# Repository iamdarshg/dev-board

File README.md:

# dev-real production board

Self-contained KiCad 9 project: board, schematics, project rules, and referenced
libraries. Open `dev-real-production.kicad_pro` for the production board; keep the
project file beside the board so DRC uses the intended rules.

## Current measured status (2026-11-04)

The repaired production board is at **10 DRC warnings, 0 errors, and 0
unconnected items**. This is not yet fab-ready. The warning breakdown is:

- 1 intentional JTDI dangling-track warning (deletion breaks a real connection)
- 2 intentional `/Power/SW` stacked microvia/blind-buried warnings requiring JLC HDI confirmation
- 2 intentional silk-only library mismatch warnings (RANT1/CANT1; shared-library deviations)
- 5 copper-sliver warnings requiring KiCad PCB Editor marker inspection

The ten hole-to-hole violations were fixed with KiCad-native geometry edits and
fresh DRC verification. The repaired board and library changes remain working-tree
state. Detailed evidence is in:
`../../evidence/dev-board/GEOMETRY_REPAIR_2026-11-02.md`.

A regenerated but not release-approved fabrication package is in:
`../../evidence/dev-board/fab-2026-11-02/`. Do not promote it to `E:\final order`
until the slivers and JLC stackup questions are closed.

---

## 1. Routing complete (historical)

All 14 unconnected items from the previous pass (was 499 originally) have
been resolved, including the last 6 hold-outs around the U13 radar BGA
corner (GND ball M12, an In2/GND stub near (56.9, 16.0), C34 pad 1, U21 pad
26, a split GND plane island on In1, and an NRESET In1↔F gap) — these needed
hand-routing (via-in-pad style connections plus small shoves of a couple of
neighboring nets — FT_RXD, GPIO_4 — that were routed directly under the
affected pads) since the escape-track congestion in that corner defeats the
interactive shove router's default settings. `Inspect → Design Rules
Checker → Run DRC` now reports **0 errors, 0 unconnected** with zones
refilled.

If future edits reintroduce unconnected items, the same workflow applies:

1. Open `dev-real.kicad_pro` → PCB Editor.
2. `Route → Interactive Router Settings…` → set **Mode: Shove** (Walk Around
   struggles near the U13 BGA corner, where several nets route directly
   under neighboring balls).
3. `Inspect → Design Rules Checker → Run DRC`, open the **Unconnected
   Items** tab, double-click an item to zoom to it.
4. Hover the pad → press `X` → route → double-click to finish. Press `V`
   mid-route to drop a via and switch layers.
5. Press `B` to refill all zones before the final DRC check — stale zone
   fill after a track/via edit can itself show up as a false clearance
   violation until refilled.

## 2. Fix SCOPE_BIAS in the schematic

`/AD9609/SCOPE_BIAS` has **no DC reference** anywhere in the schematic — the net
floats on the real board. Open `ad9609bcpzrl7_80_breakout.kicad_sch` and define
the intended bias source, then `Tools → Update PCB from Schematic` (F8).

## 3. Sanity-check before you save

After any edit: press `B` to refill zones, then `Inspect → Design Rules
Checker → Run DRC` and confirm it still reads **0 errors, 0 unconnected**
before `Ctrl+S`.

---

### Design rules already in effect (don't change)

Signal 0.127 mm / vias 0.254 mm with 0.127 mm drill / clearance 0.08 mm /
min through-drill 0.127 mm. Power rails run 0.2–0.5 mm.
The 0.2/0.1 vias on this board are **microvias** — place a new *through*-via
that small and DRC will (correctly) reject it.

### What's in here

- `dev-real.kicad_pcb` — the board
- `dev-real.kicad_pro` — project + design rules (**keep beside the board**;
  without it KiCad invents default rules and DRC becomes meaningless)
- `dev-real.kicad_sch` + 8 hierarchical sheets — full schematic
- `fp-lib-table`, `sym-lib-table` + the custom symbol/footprint libraries they
  reference (AD9609, IWRL6432, MM8108, THS8136, XCC1352, ICM-42670, ENS161,
  MMC5633, plus the project's `.pretty` footprint dirs)

Verified standalone: netlist exports all 318 components across the 9-sheet
hierarchy, and DRC output is identical to the working copy.

Full history, method, DRC report, renders and the routing scripts stay in
`D:\dev-real-updated\dev-real-updated\dev-real-routing-finish\`.

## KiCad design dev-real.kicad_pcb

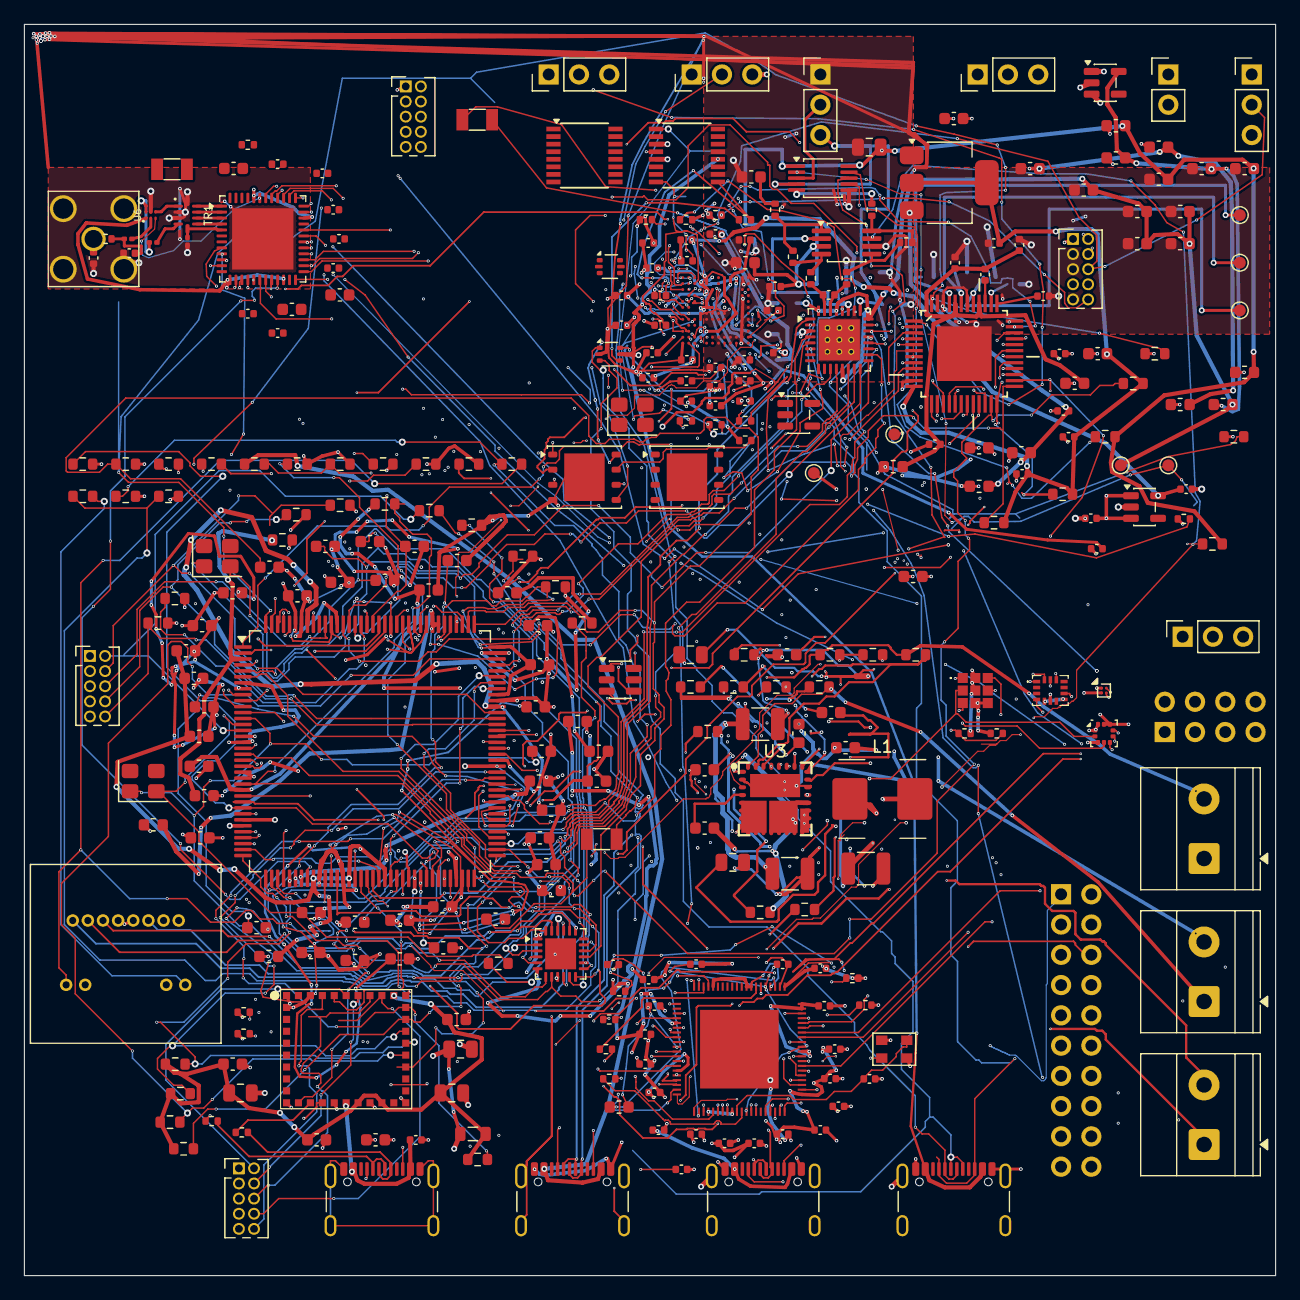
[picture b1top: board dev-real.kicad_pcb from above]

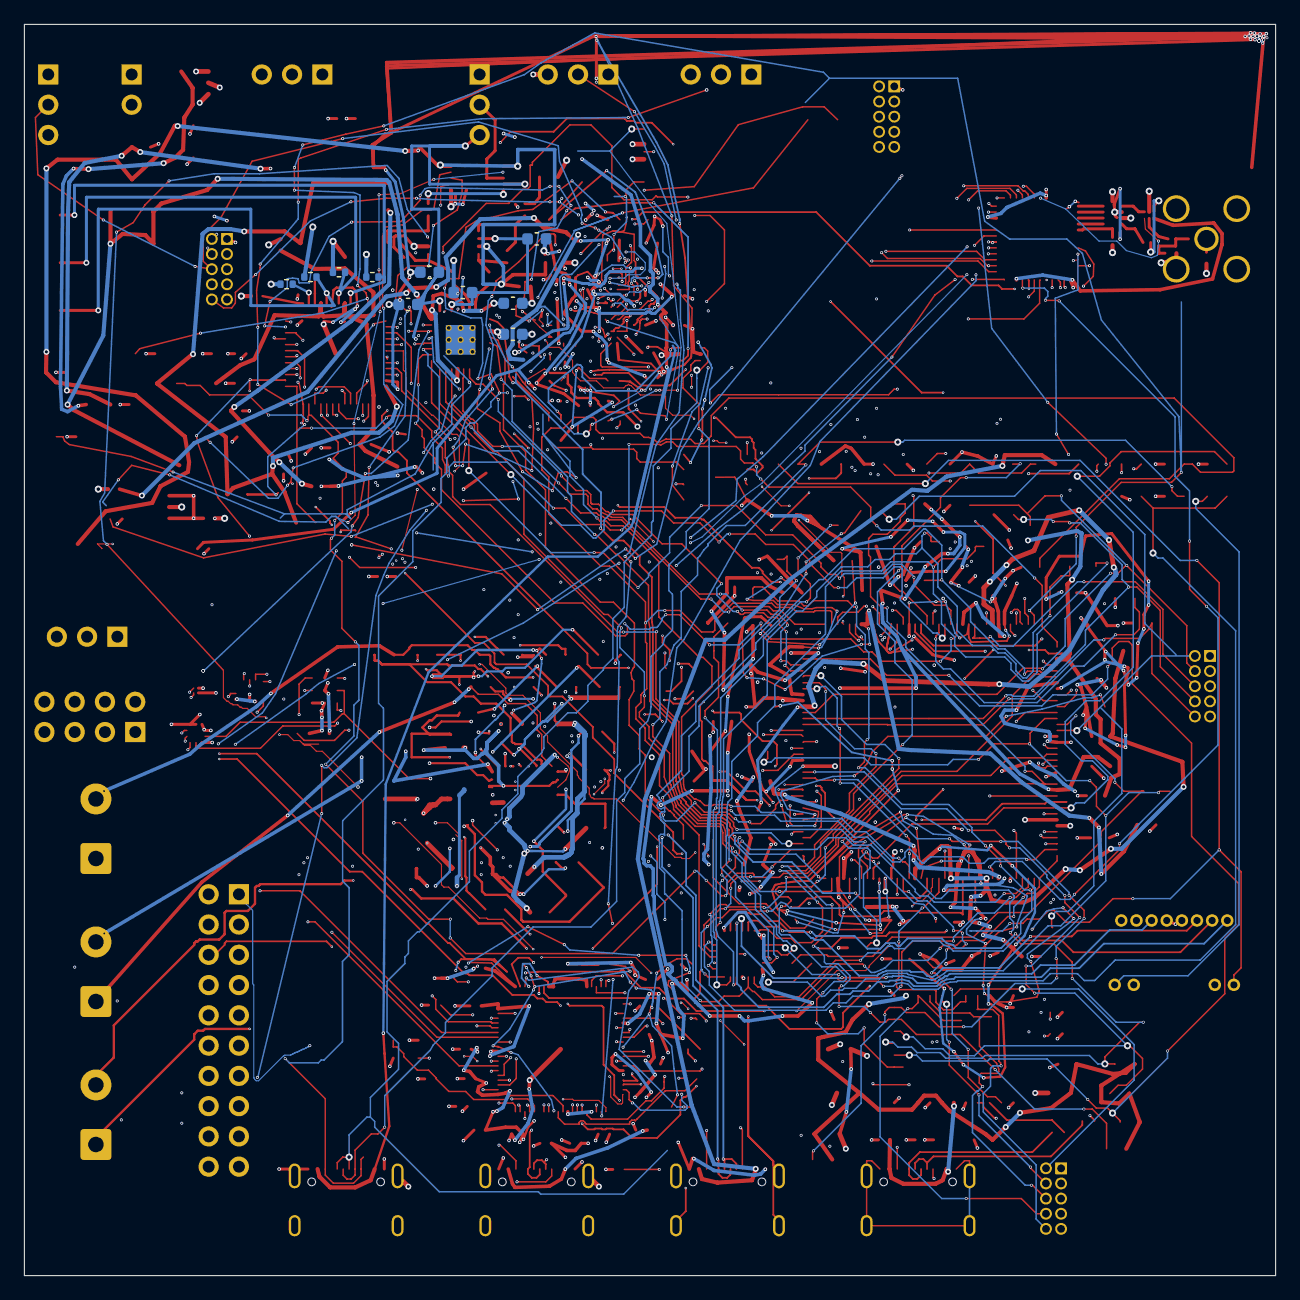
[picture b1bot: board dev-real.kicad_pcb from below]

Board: 4 copper layers, 105.0 x 105.0 mm, 318 parts (10 on the bottom side), 304 nets.

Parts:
C1: 4.7uF / >=10V; C_0805_2012Metric
C2: 2.2uF / >=10V; C_0603_1608Metric
C3, C5, C65, C69, C70, C75, C98, C99, C102, C106, C107, C109, C110, C112, C113, C114, C115, C116, C119, C120, C121, C122, C123, C124, C125, C126, C129, C130, C134: 100nF; C_0603_1608Metric
C4, C135: 4.7nF; C_0603_1608Metric
C6, C7: 15pF C0G; C_0402_1005Metric
C8, C9, C10: 4.7uF 6.3V X5R; C_0402_1005Metric
C11, C12, C14, C16, C17, C20, C34, C35, C45: 0.1uF; C_0402_1005Metric
C13, C15, C18: 22uF; C_0603_1608Metric
C19, C26, C27, C37, C40, C49, C54, C61: 1uF; C_0402_1005Metric
C21, C22, C23: 100pF; C_0201_0603Metric
C24, C25: 4.7pF; C_0402_1005Metric
C28, C39: 0.22uF; C_0402_1005Metric
C29, C30: 22pF; C_0402_1005Metric
C31, C33, C41, C42, C43: 2.2uF; C_0402_1005Metric
C32: 0.047uF; C_0402_1005Metric
C36, C38, C44, C46, C47: 10uF; C_0402_1005Metric
C48: 4.7uF; C_0402_1005Metric
C50, C52, C53, C60, C71, C76, C77, C83: 10uF; C_0603_1608Metric
C51, C55, C56, C57, C58, C59, C62, C63: 100nF; C_0402_1005Metric
C64, C67, C74: 10uF; C_0805_2012Metric
C66: 22uF; C_0805_2012Metric
C68, C78, C84, C89, C103, C118, C131, C132: 1uF; C_0603_1608Metric
C72, C79, C81, C85, C86, C87, C88, C92, C93: 100n; C_0603_1608Metric
C73: 100nF BIAS; C_0603_1608Metric
C80: 100nF AVDD; C_0603_1608Metric
C82: 100nF DVDD; C_0603_1608Metric
C90: 100nF VDD; C_0603_1608Metric
C91: 100nF VOCM; C_0603_1608Metric
C94: 1nF VDD HF; C_0402_1005Metric
C95: 22pF C0G; C_0402_1005Metric
C96, C101: 12pF; C_0603_1608Metric
C97, C105, C111: 2.2uF low-ESR; C_0603_1608Metric
C100, C104: 4.7uF; C_0603_1608Metric
C108, C117: 6.8pF; C_0603_1608Metric
C127, C128: 18pF; C_0603_1608Metric
C133: 2.2uF; C_0603_1608Metric
CANT1, CANT2: DNP; C_0402_1005Metric
CIN1: 10uF / >=10V; C_1210_3225Metric
CIN2: 39uF / >=10V; C_1210_3225Metric
COUT1: 47uF / >=6.3V; C_1210_3225Metric
COUT2: 100uF / >=6.3V; C_TODO_SELECT_100uF
CSS1: 12nF; C_0603_1608Metric
CSVIN1: 1uF / >=10V; C_0805_2012Metric
C_ADC1: 100nF; C_0402_1005Metric
C_DVDD1, C_DVDD2, C_DVDD3: 100nF; C_0402_1005Metric
C_IOBULK1: 10uF; C_0402_1005Metric
C_IOVDD1, C_IOVDD2, C_IOVDD3, C_IOVDD4, C_IOVDD5, C_IOVDD6, C_IOVDD7, C_IOVDD8: 100nF; C_0402_1005Metric
C_QSPI1: 100nF; C_0402_1005Metric
C_USB1, C_USB2: 100nF; C_0402_1005Metric
C_USBOTP1: 100nF; C_0402_1005Metric
FB1, FB2, FB4, FB5, FB6: 600R@100MHz; L_0603_1608Metric
FB3: 600R@100MHz; L_0805_2012Metric
FB7, FB8, FB9: 600R@100MHz; L_0603_1608Metric_Pad0.95x0.95mm_HandSolder
IC1: ICM-42670-P; ICM42670P
IC2: ENS161-BLGT_LGA9_T&R_1k5; ENS161BLGTLGA9TR1k5
J1: VIN_IN; TerminalBlock_Phoenix_MKDS-1,5-2_1x02_P5.00mm_Horizontal
J2: TP_EN_PG; TerminalBlock_Phoenix_MKDS-1,5-2_1x02_P5.00mm_Horizontal
J3: TP_SW_FB; TerminalBlock_Phoenix_MKDS-1,5-2_1x02_P5.00mm_Horizontal
J4, J17: USB-C Receptacle USB2; USB_C_Receptacle_GCT_USB4105-xx-A_16P_TopMnt_Horizontal
J5: Conn_01x03_Pin; PinSocket_1x03_P2.54mm_Vertical
J6: ARM_Cortex_Debug_10; PinHeader_2x05_P1.27mm_Vertical
J7: SMA_ANT_50OHM; SMA_Molex_73251-2120_EdgeMount_Horizontal
J8: 3V3_IN; PinHeader_1x02_P2.54mm_Vertical
J10: USB-C USB2 DEBUG; USB_C_Receptacle_GCT_USB4105-xx-A_16P_TopMnt_Horizontal
J11, J16: ARM_JTAG_10; PinHeader_2x05_P1.27mm_Vertical
J12: SOP0_SELECT; PinHeader_1x03_P2.54mm_Vertical
J13: SOP1_SELECT; PinHeader_1x03_P2.54mm_Vertical
J14, J15: Conn_01x03; PinHeader_1x03_P2.54mm_Vertical
J18: Conn_01x03_Pin; PinHeader_1x03_P2.54mm_Vertical
J19: Cortex SWD/JTAG; PinHeader_2x05_P1.27mm_Vertical
J20: USB-C USB2 DEVICE; USB_C_Receptacle_GCT_USB4105-xx-A_16P_TopMnt_Horizontal
J21: HR911105A MAGJACK; RJ45_Hanrun_HR911105A
J22: Conn_02x10_Counter_Clockwise; PinHeader_2x10_P2.54mm_Vertical
J23: Conn_02x04_Odd_Even; PinHeader_2x04_P2.54mm_Vertical
L1: 1uH LMLP07C7M1R0DTAS, Idc 15A / Isat 20A; L_Kyocera_LMLP07C7D_7.3x6.6mm
L2: 3.3uH Abracon AOTA-B201610S3R3-101-T; L_Abracon_AOTA-B201610S_2.0x1.6mm
NT1: AGND_to_PGND_single_point; NetTie-2_SMD_Pad0.5mm
R1, R35, R43, R46, R47, R48, R49, R62: 100k; R_0603_1608Metric
R2: 60.4k; R_0603_1608Metric
R3, R4: 2R; R_0603_1608Metric
R5: 24.3k; R_0603_1608Metric
R6, R70, R71: 1k; R_0402_1005Metric
R7, R8, R28, R29: 27R; R_0402_1005Metric
R9: 33R 1%; R_0402_1005Metric
R10: 100k; R_0402_1005Metric
R11, R12: 10k; R_0402_1005Metric
R13, R14: 27; R_0402_1005Metric
R15, R16: 0; R_0402_1005Metric
R17: 47.5k; R_0402_1005Metric
R18, R19: 2M; R_0402_1005Metric
R20, R21, R22: 75R; R_0402_1005Metric
R23, R24, R25, R27: 2.2k; R_0603_1608Metric
R26: 3.8k; R_0402_1005Metric
R30, R31, R32, R33, R34: 47k; R_0603_1608Metric
R36, R37, R39, R40: 1k 0.1%; R_0402_1005Metric
R38: 10k 1%; R_0603_1608Metric
R41, R42: 33R; R_0402_1005Metric
R44, R50: 0R; R_0603_1608Metric
R45, R65: 1M; R_0603_1608Metric
R51, R52, R53, R54, R55, R57: 10k; R_0603_1608Metric
R56: 1.5k; R_0603_1608Metric
R58, R59: 22R; R_0603_1608Metric
R60: 100R; R_0603_1608Metric
R61: 12.1k 1%; R_0603_1608Metric
R63, R64: 5.1k; R_0603_1608Metric
R66, R67: 330R; R_0603_1608Metric
R68, R69: 10k STRAP LOW; R_0603_1608Metric
RANT1: 0R; R_0402_1005Metric
RBOT1: 665R; R_0603_1608Metric
RCC1, RCC2, RCC3, RCC4: 5.1k; R_0402_1005Metric
RCL1: 2.21k; R_0603_1608Metric
REN1: 100k; R_0603_1608Metric
REXTVDD1: 0R DNP/NC option; R_0603_1608Metric
RPG1: 10k; R_0603_1608Metric
RTOP1: 3.00k; R_0603_1608Metric
TP1: AR_TP; TestPoint_Pad_D1.0mm
TP2: AG_TP; TestPoint_Pad_D1.0mm
TP3: AB_TP; TestPoint_Pad_D1.0mm
TP4, TP5: VCM; TestPoint_Pad_D1.0mm
TP6: VREF; TestPoint_Pad_D1.0mm
TP7: AVDD_1V8; TestPoint_Pad_D1.0mm
TR1: 0900PC15A0036; Johanson_0900PC15A0036_0805_10Pin
U1: MMC5633NJL; WLP-4_0.86x0.86mm_P0.4mm
U2: LPS22HH; ST_HLGA-10_2x2mm_P0.5mm_LayoutBorder3x2y
U3: MIC28516T-E/PHA; MIC28516-VQFN-32-6x6mm-P0.65-MultipleEP
U4: RP2350B; RP2350B_QFN80_10x10mm_P0.4mm_EP
U5: XCC1352R1F3RGZR; VQFN-48-1EP_7x7mm_P0.5mm_EP5.15x5.15mm
U6: XMSSJJ3G0PA-054; Murata_XMSSJJ3G0PA-054
U7: TLV75518PDBV; SOT-23-5
U8: TLV75518PDBVR; SOT-23-5
U9, U10: USBLC6-2P6; SOT-666
U11, U12: FT230XS-R; SSOP-16_3.9x4.9mm_P0.635mm
U13: IWRL6432BDBAAMFR; IWRL6432_AMF_FCCSP-102_6.45x6.45mm_P0.50mm
U14, U15: MX25R1635FZUIH0; WSON-8-1EP_6x5mm_P1.27mm_EP3.4x4mm
U16: AMS1117-1.8; SOT-223-3_TabPin2
U17: THS8136; QFP50P900X900X120-49N
U18: MM8108-MF15457; MM8108MF15457
U19: AP2112K-1.8; SOT-23-5
U20: PGA113AIDGSR; VSSOP-10_3x3mm_P0.5mm
U21: AD9609BCPZRL7-80; QFN-32-1EP_5x5mm_P0.5mm_EP3.45x3.45mm_ThermalVias
U22: MCP6D11T-E/MS; MSOP-8_3x3mm_P0.65mm
U23: STM32H7S3Z8T6; LQFP-144_20x20mm_P0.5mm
U24: LAN8742A-CZ-TR; QFN-24-1EP_4x4mm_P0.5mm_EP2.6x2.6mm
U25: USBLC6-2SC6; SOT-23-6
Y1: 12MHz ABM8-272-T3; Crystal_ABM8_3.2x2.5mm
Y2: 48MHz; Crystal_SMD_3225-2Pin_3.2x2.5mm
Y3: 40MHz; Crystal_SMD_3225-2Pin_3.2x2.5mm
Y4: 40MHz; Crystal_SMD_3225-4Pin_3.2x2.5mm
Y5: 24MHz; Crystal_SMD_3225-4Pin_3.2x2.5mm
Y6: 32.768kHz; Crystal_SMD_3215-2Pin_3.2x1.5mm
Y7: 25MHz; Crystal_SMD_3225-4Pin_3.2x2.5mm

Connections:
+3V3: C4.1, C8.1, C26.2, C31.2, C36.2, C45.2, C49.2, C50.2, C51.2, C64.1, C65.1, C71.2, C72.2, C98.1, C99.1, C100.1, C106.1, C107.1, C112.1, C113.1, C115.1, C116.1, C120.1, C121.1, C124.1, C125.1, C130.1, C131.1, COUT1.1, COUT2.1, C_ADC1.1, C_IOBULK1.1, C_IOVDD1.1, C_IOVDD2.1, C_IOVDD3.1, C_IOVDD4.1, C_IOVDD5.1, C_IOVDD6.1, C_IOVDD7.1, C_IOVDD8.1, C_QSPI1.1, C_USBOTP1.1, FB1.1, FB2.1, FB3.1, FB4.1, FB5.1, FB7.1, FB8.1, FB9.1, IC1.5 (VDDIO), IC1.8 (VDD), IC2.4 (VDD), IC2.5 (VDDIO), J6.1, J11.1, J14.3, J15.3, J19.9, J21.4, J21.5, J22.2, J22.3, J23.6, L1.2, R9.1, R12.1, R17.1, R18.1, R19.1, R44.2, R46.2, R49.2, R51.2, R53.2, R54.2, R55.2, R56.2, R57.2, R71.1, RTOP1.1, U1.B1 (VDD), U2.1 (Vdd_IO), U2.10 (VDD), U4.5, U4.15, U4.24, U4.29, U4.41, U4.50, U4.59, U4.60, U4.64, U4.68, U4.69, U4.76, U5.13 (VDDS2), U5.22 (VDDS3), U5.34 (VDDS_DCDC), U5.44 (VDDS), U6.1, U7.1 (IN), U7.3 (EN), U12.3 (VCCIO), U13.G12 (VIOIN), U13.M11 (VIOIN), U14.8 (VCC), U19.1 (VIN), U19.3 (EN), U23.7 (VDD), U23.17 (VDD), U23.31 (VDD), U23.41 (VDD), U23.69 (VDD), U23.81 (VDD), U23.88 (VDD), U23.100 (VDD), U23.108 (VDD), U23.123 (VDD), U23.133 (VDD), U23.139 (VDD), U24.1 (VDD2A), U24.9 (VDDIO), U24.19 (VDD1A)
/AD9609/3V3_AFE: C74.2, C75.2, C80.2, C82.2, C90.2, C94.2, FB4.2, R35.2, R43.2, U20.1 (AVDD), U20.10 (DVDD), U22.3 (VDD)
/AD9609/ADC_VIN_N: C95.1, R42.1, U21.30 (VIN-)
/AD9609/ADC_VIN_P: C95.2, R41.1, U21.31 (VIN+)
/AD9609/AVDD_1V8: C83.2, C84.2, C85.2, C86.2, C87.2, C88.2, FB6.2, TP7.1, U21.13 (DRVDD), U21.24 (AVDD), U21.29 (AVDD), U21.32 (AVDD)
/AD9609/CLK_N: U21.2 (CLK-), U23.61 (PP1)
/AD9609/CLK_P: U21.1 (CLK+), U23.55 (PP0)
/AD9609/CSB: U21.4 (CSB), U23.83 (PD15)
/AD9609/D0: U21.11 (D0), U23.104 (PD0)
/AD9609/D1: U21.12 (D1), U23.105 (PD1)
/AD9609/D2: U21.14 (D2), U23.71 (PD12)
/AD9609/D3: U21.15 (D3), U23.109 (PD3)
/AD9609/D4: U21.16 (D4), U23.129 (PD5)
/AD9609/D5: U21.17 (D5), U23.130 (PD6)
/AD9609/D6: U21.18 (D6), U23.131 (PD7)
/AD9609/D7: U21.19 (D7), U23.65 (PD8)
/AD9609/D8: U21.20 (D8), U23.66 (PD9)
/AD9609/D9: U21.21 (D9), U23.67 (PD10)
/AD9609/DCO: U21.22 (DCO), U23.68 (PD11)
/AD9609/DRVDD_3V3: C76.2, C78.2, C81.2, FB5.2, U21.3 (AVDD)
/AD9609/LDO_1V8: C77.2, C79.2, FB6.1, U19.5 (VOUT)
/AD9609/MCP_IN_N: R36.1, R39.2, U22.1 (IN-)
/AD9609/MCP_IN_P: R37.1, R40.2, U22.8 (IN+)
/AD9609/MCP_OUT_N: R40.1, R42.2, U22.5 (OUT-)
/AD9609/MCP_OUT_P: R39.1, R41.2, U22.4 (OUT+)
/AD9609/MODE_OR: U21.23 (MODE/OR), U23.82 (PD14)
/AD9609/PGA_OUT: R37.2, U20.5 (VOUT)
/AD9609/RBIAS: R38.2, U21.28 (RBIAS)
/AD9609/SCLK_DFS: U21.5 (SCLK/DFS), U23.72 (PD13)
/AD9609/SCOPE_BIAS: C73.2, R36.2
/AD9609/SCOPE_DRIVER_PD_N: R43.1, U22.7 (~PD), U23.54 (PP5)
/AD9609/SCOPE_PGA_CS_N: R35.1, U20.9 (~CS), U23.47 (PP4)
/AD9609/SCOPE_PGA_DIO: U20.8 (DIO), U23.49 (PP3)
/AD9609/SCOPE_PGA_SCLK: U20.7 (SCLK), U23.48 (PP2)
/AD9609/SDIO_PDWN: U21.6 (SDIO/PDWN), U23.58 (PP6)
/AD9609/VCM: C91.2, C93.2, TP5.1, U21.27 (VCM), U22.2 (VOCM)
/AD9609/VREF: C89.2, C92.2, J18.3, TP6.1, U20.4 (VREF), U21.25 (VREF)
/IWRL6432BD/1V8: C27.2, C39.2, C42.2, C46.2, U7.5 (OUT), U13.C6 (VIOIN_18CLK), U13.C8 (VIOIN_18), U13.F3 (VDDA_18VCO), U13.J5 (VIN_18PM), U13.K12 (VIOIN_18), U13.L5 (VDDA_18BB), U13.L8 (VIOIN_18), U13.M5 (VDDA_18BB), U13.M8 (VIOIN_18)
/IWRL6432BD/FT_RXD: R16.1, U12.4 (RXD)
/IWRL6432BD/FT_TXD: R15.1, U12.1 (TXD)
/IWRL6432BD/FT_USBDM: C29.2, R13.2, U12.9 (USBDM)
/IWRL6432BD/FT_USBDP: C30.2, R14.2, U12.8 (USBDP)
/IWRL6432BD/GPIO_0: U4.16, U13.B12 (SPIA_MOSI/GPIO_0)
/IWRL6432BD/GPIO_1: U4.17, U13.C11 (SPIA_MISO/GPIO_1)
/IWRL6432BD/GPIO_2: U4.18, U13.H10 (GPIO_2)
/IWRL6432BD/GPIO_3: U4.19, U13.J11 (UARTA_RX/GPIO_3)
/IWRL6432BD/GPIO_4: U4.20, U13.K11 (NERROR_OUT/GPIO_4)
/IWRL6432BD/GPIO_5: U4.21, U13.J10 (GPIO_5)
/IWRL6432BD/GPIO_6: U4.22, U13.L11 (UARTA_RTS/GPIO_6)
/IWRL6432BD/GPIO_7: U4.23, U13.M10 (HOST_CLK_REQ/GPIO_7)
/IWRL6432BD/JTAG_TCK: J11.4, U13.C12 (TCK)
/IWRL6432BD/JTAG_TDI: J11.8, U13.G11 (TDI)
/IWRL6432BD/JTAG_TMS: J11.2, U13.E12 (TMS)
/IWRL6432BD/NRESET: C28.2, J11.10, R12.2, U13.L10 (NRESET)
/IWRL6432BD/PMIC_CLKOUT_SOP1: J15.2, U13.H11 (PMIC_CLKOUT/SOP1)
/IWRL6432BD/QSPI_CLK: U13.A11 (QSPI_CLK), U14.6 (SCLK)
/IWRL6432BD/QSPI_CS: R17.2, U13.A10 (QSPI_CS), U14.1 (CS#)
/IWRL6432BD/QSPI_D0: U13.B11 (QSPI[0]), U14.5 (SI/SIO0)
/IWRL6432BD/QSPI_D1: U13.B8 (QSPI[1]), U14.2 (SO/SIO1)
/IWRL6432BD/QSPI_D2: R18.2, U13.B10 (QSPI[2]), U14.3 (WP#/SIO2)
/IWRL6432BD/QSPI_D3: R19.2, U13.B9 (QSPI[3]), U14.7 (RESET#/SIO3)
/IWRL6432BD/RADAR_1P2_RF: C41.2, C44.2, U13.L4 (VDDA_12RF), U13.M4 (VDDA_12RF)
/IWRL6432BD/RADAR_1V2_INT: C48.2, U13.C9 (VDD), U13.G7 (VDD), U13.G8 (VDD), U13.G9 (VDD), U13.H8 (VDD), U13.K7 (VDD)
/IWRL6432BD/RADAR_1V4_APLL: C37.2, U13.G5 (VOUT_14APLL)
/IWRL6432BD/RADAR_1V4_SYNTH: C40.2, U13.D3 (VOUT_14SYNTH)
/IWRL6432BD/RADAR_1V_RF_OUT: C33.2, C38.2, U13.L3 (VDDA_10RF), U13.M3 (VDDA_10RF)
/IWRL6432BD/RADAR_SRAM_1V2: C43.2, C47.2, U13.L9 (VNWA), U13.M7 (VDD_SRAM)
/IWRL6432BD/RADAR_VBGAP: C32.2, U13.H5 (VBGAP)
/IWRL6432BD/RDIF_D2: U4.25, U13.L12 (UARTA_TX)
/IWRL6432BD/RS232_RX: R15.2, U13.F11 (RS232_RX)
/IWRL6432BD/RS232_TX: R16.2, U13.E10 (RS232_TX)
/IWRL6432BD/TDO_SOP0: J11.6, J14.2, U13.E11 (TDO/SOP0)
/IWRL6432BD/USB_DM_CONN: J10.A7 (D-), J10.B7 (D-), U9.3 (I/O2)
/IWRL6432BD/USB_DP_CONN: J10.A6 (D+), J10.B6 (D+), U9.1 (I/O1)
/IWRL6432BD/USB_ID: J10.A5 (CC1), J10.B5 (CC2), R11.1
/IWRL6432BD/USB_VBUS: C34.2, J10.A4 (VBUS), J10.A9 (VBUS), J10.B4 (VBUS), J10.B9 (VBUS), U9.5 (VBUS), U12.12 (VCC)
/IWRL6432BD/XTALM: C24.2, U13.B1 (CLKM), Y3.1
/IWRL6432BD/XTALP: C25.2, U13.D1 (CLKP), Y3.2
/MM8108/3V3_MM8108: C66.1, C67.1, C68.1, C69.1, C70.1, FB3.2, R30.1, R31.1, R32.1, R33.1, R34.1, U18.10 (VBAT), U18.22 (VDDIO), U18.24 (VBAT_TX)
/MM8108/BUSY: U18.29 (BUSY), U23.59 (PO2)
/MM8108/JTAG_TCK: J16.4, U18.7 (JTAG_TCK/GPIO13)
/MM8108/JTAG_TDI: J16.8, U18.9 (JTAG_TDI/GPIO14)
/MM8108/JTAG_TMS: J16.2, U18.6 (JTAG_TMS/GPIO15)
/MM8108/NRESET: J16.10, U18.4 (RESET_N)
/MM8108/SDIO_CLK_SPI_SCK: U18.17 (SDIO_CLK/SPI_SCK), U23.103 (PC12)
/MM8108/SDIO_CMD_SPI_MOSI: R34.2, U18.16 (SDIO_CMD/SPI_MOSI), U23.106 (PD2)
/MM8108/SDIO_D0_SPI_MISO: R30.2, U18.12 (SDIO_D0/SPI_MISO), U23.86 (PC8)
/MM8108/SDIO_D1_SPI_INT: R31.2, U18.14 (SDIO_D1/SPI_INT), U23.87 (PC9)
/MM8108/SDIO_D2: R32.2, U18.15 (SDIO_D2), U23.101 (PC10)
/MM8108/SDIO_D3_SPI_CS: R33.2, U18.13 (SDIO_D3/SPI_CS), U23.102 (PC11)
/MM8108/TDO_SOP0: J16.6, U18.8 (JTAG_TDO/GPIO16)
/MM8108/WAKE: U18.5 (WAKE), U23.53 (PO4)
/Power/AGND: CSS1.2, CSVIN1.2, NT1.1, R2.2, RBOT1.2, U3.28
/Power/BST: C3.1, U3.4
/Power/EN: J2.2, REN1.2, U3.24
/Power/EXTVDD: REXTVDD1.1, U3.23
/Power/FB: C4.2, C5.2, J3.1, RBOT1.1, RTOP1.2, U3.27
/Power/FREQ: R1.2, R2.1, U3.25
/Power/ILIM: RCL1.1, U3.1
/Power/MODE_SS: CSS1.1, U3.26
/Power/PG: J2.1, RPG1.2, U3.32
/Power/PVDD: C1.1, R4.2, U3.21
/Power/RIPPLE_INJ: C5.1, R5.2
/Power/SVIN: CSVIN1.1, R3.2, U3.31
/Power/SW: C3.2, J3.2, L1.1, R5.1, RCL1.2, U3.3, U3.12, U3.13, U3.14, U3.15, U3.20
/Power/VDD: C2.1, R4.1, REN1.1, RPG1.1, U3.30
/Power/VIN: CIN1.1, CIN2.1, J1.2, R1.1, R3.1, U3.5, U3.6, U3.7, U3.8, U3.9, U3.10, U3.11
/RP2350/+1V1: C9.1, C_DVDD1.1, C_DVDD2.1, C_DVDD3.1, L2.2, U4.10, U4.32, U4.51, U4.65
/RP2350/CC1: J4.A5 (CC1), RCC1.1
/RP2350/CC2: J4.B5 (CC2), RCC2.1
/RP2350/GPIO0: U4.77, U23.93 (PA11)
/RP2350/GPIO1: U4.78, U23.94 (PA12)
/RP2350/GPIO2: U4.79, U5.10 (DIO_5)
/RP2350/GPIO3: U4.80, U5.14 (DIO_8)
/RP2350/GPIO4: U4.1, U5.11 (DIO_6)
/RP2350/GPIO6: U4.3, U5.15 (DIO_9)
/RP2350/GPIO7: U4.4, U5.9 (DIO_4)
/RP2350/GPIO8: U4.6, U5.8 (DIO_3)
/RP2350/GPIO9: U4.7, U23.29 (PA3)
/RP2350/GPIO10: U4.8, U23.32 (PA4)
/RP2350/GPIO11: U4.9, U23.33 (PA5)
/RP2350/GPIO12: U4.11, U23.34 (PA6)
/RP2350/GPIO13: U4.12, U23.90 (PA8)
/RP2350/GPIO14: U4.13, U23.91 (PA9)
/RP2350/GPIO15: U4.14, U23.92 (PA10)
/RP2350/GPIO25: U2.7 (INT_DRDY), U4.26
/RP2350/GPIO26: IC1.4 (INT1_/_INT), U4.27
/RP2350/GPIO27: IC1.9 (INT2), U4.28
/RP2350/GPIO28: IC2.6 (INTN), U4.36
/RP2350/GPIO29: J23.4, U4.37
/RP2350/GPIO30: U1.B2 (SDA), U4.38
/RP2350/GPIO31: U1.A2 (SCL), U4.39
/RP2350/GPIO32: IC1.1 (AP_SDO_/_AP_AD0), U4.40
/RP2350/GPIO33: IC1.12 (AP_CS), U4.42
/RP2350/GPIO34: IC1.13 (AP_SCL_/_AP_SCLK), U4.43
/RP2350/GPIO35: IC1.14 (AP_SDA_/_AP_SDIO_/_AP_SDI), U4.44
/RP2350/GPIO36: IC2.1 (MOSI_/_SDA), U2.4 (SDA), U4.45
/RP2350/GPIO37: IC2.2 (SCLK_/_SCL), U2.2 (SCL), U4.46
/RP2350/GPIO38: IC2.7 (CSN), U4.47
/RP2350/GPIO39: U2.6 (~CS), U4.48
/RP2350/GPIO40_ADC0: U2.5 (SA0), U4.49
/RP2350/GPIO41_ADC1: IC2.3 (MISO_/_ADDR), U4.52
/RP2350/GPIO42_ADC2: R70.1, R71.2, U4.53
/RP2350/GPIO43_ADC3: J23.7, U4.54
/RP2350/GPIO44_ADC4: J23.5, U4.55
/RP2350/GPIO45_ADC5: J23.3, U4.56
/RP2350/GPIO46_ADC6: J23.1, U4.57
/RP2350/GPIO47_ADC7: J23.2, U4.58
/RP2350/SWCLK: J5.3, U4.33
/RP2350/SWDIO: J5.1, U4.34
/RP2350/USB_DM_IC: R8.1, U4.66
/RP2350/USB_DP_IC: R7.1, U4.67
/RP2350/USB_D_N_CONN: J4.A7 (D-), J4.B7 (D-), R8.2
/RP2350/USB_D_P_CONN: J4.A6 (D+), J4.B6 (D+), R7.2
/RP2350/USB_VBUS: C_USB1.1, J4.A4 (VBUS), J4.A9 (VBUS), J4.B4 (VBUS), J4.B9 (VBUS)
/RP2350/VREG_AVDD: C10.1, R9.2, U4.61
/RP2350/VREG_LX: L2.1, U4.63
/RP2350/XIN: C6.1, U4.30, Y1.2 (GND)
/RP2350/XOUT: R6.1, U4.31
/RP2350/XOUT_XTAL: C7.1, R6.2, Y1.4 (GND)
/STM32H7/3V3_USB: C132.1, C134.1, FB9.2, U23.115 (VDD50USB), U23.116 (VDD33USB)
/STM32H7/3V3_XSPI: C104.1, C110.1, C114.1, C119.1, C123.1, FB8.2, U23.45 (VDDXSPI1), U23.51 (VDDXSPI1), U23.57 (VDDXSPI1), U23.63 (VDDXSPI1)
/STM32H7/BOOT0: R47.1, U23.128 (BOOT0)
/STM32H7/ETH_CRS_DV: R55.1, U23.35 (PA7), U24.11 (CRS_DV/MODE2)
/STM32H7/ETH_LED1: R66.1, R68.1, U24.3 (LED1)
/STM32H7/ETH_LED2: R67.1, R69.1, U24.2 (LED2)
/STM32H7/ETH_MDC: U23.19 (PC1), U24.13 (MDC)
/STM32H7/ETH_MDIO: R56.1, U23.28 (PA2), U24.12 (MDIO)
/STM32H7/ETH_PHY_RESET: C126.1, R57.1, U23.110 (PD4), U24.15 (~RST)
/STM32H7/ETH_REF_CLK: U23.27 (PA1), U24.14 (~INT/REFCLKO)
/STM32H7/ETH_RXD0: R53.1, U23.36 (PC4), U24.8 (RXD0/MODE0)
/STM32H7/ETH_RXD1: R54.1, U23.37 (PC5), U24.7 (RXD1/MODE1)
/STM32H7/ETH_TXD0: U23.38 (PB0), U24.17 (TXD0)
/STM32H7/ETH_TXD1: U23.39 (PB1), U24.18 (TXD1)
/STM32H7/ETH_TX_EN: U23.74 (PB11), U24.16 (TXEN)
/STM32H7/HSE_IN: C96.1, R45.1, U23.13 (PH0), Y5.1
/STM32H7/HSE_OUT: C101.1, R45.2, U23.14 (PH1), Y5.2
/STM32H7/JTDI: J19.4, R49.1, U23.97 (PA15)
/STM32H7/LSE_IN: C108.1, U23.5 (PC14), Y6.1
/STM32H7/LSE_OUT: C117.1, U23.6 (PC15), Y6.2
/STM32H7/NRST: C122.1, J19.2, R51.1, U23.15 (NRST)
/STM32H7/PB2: U17.3 (B7), U23.40 (PB2)
/STM32H7/PB5: U17.4 (B6), U23.136 (PB5)
/STM32H7/PB6: U17.5 (B5), U23.143 (PB6)
/STM32H7/PB10: U17.26 (CLK), U23.73 (PB10)
/STM32H7/PB13: U17.20 (R7), U23.76 (PB13)
/STM32H7/PB14: U17.21 (R8), U23.77 (PB14)
/STM32H7/PB15: U17.22 (R9), U23.78 (PB15)
/STM32H7/PC0: U17.10 (B0), U23.18 (PC0)
/STM32H7/PC2: U17.9 (B1), U23.20 (PC2)
/STM32H7/PC3: U17.8 (B2), U23.21 (PC3)
/STM32H7/PC6: U17.7 (B3), U23.84 (PC6)
/STM32H7/PC7: U17.6 (B4), U23.85 (PC7)
/STM32H7/PC13: U17.27 (G9), U23.4 (PC13)
/STM32H7/PE0: U17.13 (R0), U23.140 (PE0)
/STM32H7/PE1: U17.14 (R1), U23.141 (PE1)
/STM32H7/PE2: U17.15 (R2), U23.142 (PE2)
/STM32H7/PE3: U17.16 (R3), U23.9 (PE3)
/STM32H7/PE4: U17.17 (R4), U23.10 (PE4)
/STM32H7/PE5: U17.18 (R5), U23.11 (PE5)
/STM32H7/PE6: U17.19 (R6), U23.12 (PE6)
/STM32H7/PHY_RBIAS: R61.1, U24.24 (RBIAS)
/STM32H7/PHY_RXER: R52.1, U24.10 (RXER/PHYAD0)
/STM32H7/PHY_RXN: J21.6, U24.22 (RXN)
/STM32H7/PHY_RXP: J21.3, U24.23 (RXP)
/STM32H7/PHY_TXN: J21.2, U24.20 (TXN)
/STM32H7/PHY_TXP: J21.1, U24.21 (TXP)
/STM32H7/PHY_VDDCR: C133.1, U24.6 (VDDCR)
/STM32H7/PHY_XTAL1: C127.1, U24.5 (XTAL1/CLKIN), Y7.1
/STM32H7/PHY_XTAL2: C128.1, U24.4 (XTAL2), Y7.2
/STM32H7/PM0: U17.36 (G0), U23.111 (PM0)
/STM32H7/PM1: U17.35 (G1), U23.112 (PM1)
/STM32H7/PM2: U17.34 (G2), U23.113 (PM2)
/STM32H7/PM3: U17.33 (G3), U23.114 (PM3)
/STM32H7/PM5: U17.32 (G4), U23.118 (PM5)
/STM32H7/PM6: U17.31 (G5), U23.119 (PM6)
/STM32H7/PM8: U17.30 (G6), U23.121 (PM8)
/STM32H7/PM9: U17.29 (G7), U23.122 (PM9)
/STM32H7/PM13: U17.28 (G8), U23.127 (PM13)
/STM32H7/PO0: U5.20 (DIO_14), U23.64 (PO0)
/STM32H7/PO1: U5.21 (DIO_15), U23.44 (PO1)
/STM32H7/PO5: U17.2 (B8), U23.52 (PO5)
/STM32H7/PP7: U17.1 (B9), U23.60 (PP7)
/STM32H7/RJ_LED_GREEN_A: J21.9, R66.2
/STM32H7/RJ_LED_YELLOW_A: J21.12, R67.2
/STM32H7/SWCLK: J19.8, R48.1, U23.96 (PA14)
/STM32H7/SWDIO: J19.10, R46.1, U23.95 (PA13)
/STM32H7/SWO: J19.6, U23.134 (PB3)
/STM32H7/USB_CC1: J20.A5 (CC1), R63.1
/STM32H7/USB_CC2: J20.B5 (CC2), R64.1
/STM32H7/USB_CONN_DM: J20.A7 (D-), J20.B7 (D-), U25.1 (I/O1)
/STM32H7/USB_CONN_DP: J20.A6 (D+), J20.B6 (D+), U25.3 (I/O2)
/STM32H7/USB_DM_ESD: R59.1, U25.6 (I/O1)
/STM32H7/USB_DP_ESD: R58.1, U25.4 (I/O2)
/STM32H7/USB_FS_DM: R59.2, U23.124 (PM12)
/STM32H7/USB_FS_DP: R58.2, U23.125 (PM11)
/STM32H7/USB_SHIELD: C135.1, J20.S1 (Shield), R65.1
/STM32H7/USB_VBUS: J20.A4 (VBUS), J20.A9 (VBUS), J20.B4 (VBUS), J20.B9 (VBUS), R60.1
/STM32H7/USB_VBUS_SENSE: C129.1, R60.2, R62.1, U23.126 (PM14)
/STM32H7/VBAT: C102.1, R44.1, U23.3 (VBAT)
/STM32H7/VCAP1: C97.1, U23.43 (VCAP1)
/STM32H7/VCAP2: C105.1, U23.79 (VCAP2)
/STM32H7/VCAP34: C111.1, U23.98 (VCAP3), U23.137 (VCAP4)
/STM32H7/VDDA: C103.1, C109.1, FB7.2, R50.1, U23.25 (VDDA)
/STM32H7/VREFP: C118.1, R50.2, U23.24 (VREFP)
/THX8136/3V3_DVDD_PRE: C53.2, C55.2, FB1.2, U16.3 (VI)
/THX8136/AB: R22.2, TP3.1, U17.45 (AB)
/THX8136/AG: R21.2, TP2.1, U17.41 (AG)
/THX8136/AR: R20.2, TP1.1, U17.43 (AR)
/THX8136/AVDD_FILT: C52.2, C54.2, C56.2, C57.1, C58.2, FB2.2, U17.40 (AVDD), U17.44 (AVDD)
/THX8136/BLANK: R23.1, U17.23 (BLANK), U23.75 (PB12)
/THX8136/COMP: C57.2, U17.39 (COMP)
/THX8136/DVDD_1V8: C60.2, C61.2, C62.2, C63.2, R23.2, R24.2, R25.2, U16.2 (VO), U17.12 (DVDD)
/THX8136/FSADJ: R26.2, U17.38 (FSADJ)
/THX8136/M2: R27.2, U17.48 (M2), U23.144 (PB7)
/THX8136/SYNC: R24.1, U17.24 (SYNC), U23.2 (PB9)
/THX8136/SYNC_T: R25.1, U17.25 (SYNC_T), U23.1 (PB8)
/THX8136/VREF: C59.2, U17.37 (VREF)
/XCC1352R1F3RGZR/ANT_50OHM: CANT2.1, J7.1, RANT1.2
/XCC1352R1F3RGZR/ANT_MATCH_IN: C23.2, CANT1.1, RANT1.1
/XCC1352R1F3RGZR/DIO_10: J22.7, U5.16 (DIO_10)
/XCC1352R1F3RGZR/DIO_11: J22.6, U5.17 (DIO_11)
/XCC1352R1F3RGZR/DIO_12: J22.5, U5.18 (DIO_12)
/XCC1352R1F3RGZR/DIO_13: J22.4, U5.19 (DIO_13)
/XCC1352R1F3RGZR/DIO_16: J6.6, U5.26 (DIO_16), U23.26 (PA0)
/XCC1352R1F3RGZR/DIO_17: J6.8, J22.8, U5.27 (DIO_17)
/XCC1352R1F3RGZR/DIO_18: J22.9, U5.28 (DIO_18)
/XCC1352R1F3RGZR/DIO_19: J22.10, U5.29 (DIO_19)
/XCC1352R1F3RGZR/DIO_20: J22.11, U5.30 (DIO_20)
/XCC1352R1F3RGZR/DIO_21: J22.12, U5.31 (DIO_21)
/XCC1352R1F3RGZR/DIO_22: J22.13, U5.32 (DIO_22)
/XCC1352R1F3RGZR/DIO_23: J22.14, U5.36 (DIO_23)
/XCC1352R1F3RGZR/DIO_24: J22.15, U5.37 (DIO_24)
/XCC1352R1F3RGZR/DIO_25: J22.16, U5.38 (DIO_25)
/XCC1352R1F3RGZR/DIO_26: J22.17, U5.39 (DIO_26)
/XCC1352R1F3RGZR/DIO_27: J22.18, U5.40 (DIO_27)
/XCC1352R1F3RGZR/DIO_28: J22.19, U5.41 (DIO_28)
/XCC1352R1F3RGZR/DIO_29: J22.20, U5.42 (DIO_29)
/XCC1352R1F3RGZR/DIO_30: U5.43 (DIO_30), U6.3
/XCC1352R1F3RGZR/JTAG_TCKC: J6.4, U5.25 (JTAG_TCKC)
/XCC1352R1F3RGZR/JTAG_TMSC: J6.2, U5.24 (JTAG_TMSC)
/XCC1352R1F3RGZR/RESET_N: J6.10, U5.35 (RESET_N)
/XCC1352R1F3RGZR/RF_2G4_UNBAL: TR1.1, U6.4
/XCC1352R1F3RGZR/RF_COMMON: C23.1, U6.2
/XCC1352R1F3RGZR/RF_N_2_4GHZ: TR1.8, U5.2 (RF_N_2_4GHZ)
/XCC1352R1F3RGZR/RF_N_SUB_1GHZ: TR1.6, U5.4 (RF_N_SUB_1GHZ)
/XCC1352R1F3RGZR/RF_P_2_4GHZ: TR1.9, U5.1 (RF_P_2_4GHZ)
/XCC1352R1F3RGZR/RF_P_SUB_1GHZ: TR1.7, U5.3 (RF_P_SUB_1GHZ)
/XCC1352R1F3RGZR/RF_SUB1_IPC: C21.1, TR1.4
/XCC1352R1F3RGZR/RF_SUB1_SW: C21.2, U6.6
/XCC1352R1F3RGZR/RX_TX: C22.1, TR1.5, U5.5 (RX_TX)
GND: C1.2, C2.2, C6.2, C7.2, C8.2, C9.2, C10.2, C22.2, C24.1, C25.1, C26.1, C27.1, C28.1, C29.1, C30.1, C31.1, C32.1, C33.1, C34.1, C35.1, C35.2, C36.1, C37.1, C38.1, C39.1, C40.1, C41.1, C42.1, C43.1, C44.1, C45.1, C46.1, C47.1, C48.1, C49.1, C50.1, C51.1, C52.1, C53.1, C54.1, C55.1, C56.1, C58.1, C59.1, C60.1, C61.1, C62.1, C63.1, C64.2, C65.2, C66.2, C67.2, C68.2, C69.2, C70.2, C71.1, C72.1, C73.1, C74.1, C75.1, C76.1, C77.1, C78.1, C79.1, C80.1, C81.1, C82.1, C83.1, C84.1, C85.1, C86.1, C87.1, C88.1, C89.1, C90.1, C91.1, C92.1, C93.1, C94.1, C96.2, C97.2, C98.2, C99.2, C100.2, C101.2, C102.2, C103.2, C104.2, C105.2, C106.2, C107.2, C108.2, C109.2, C110.2, C111.2, C112.2, C113.2, C114.2, C115.2, C116.2, C117.2, C118.2, C119.2, C120.2, C121.2, C122.2, C123.2, C124.2, C125.2, C126.2, C127.2, C128.2, C129.2, C130.2, C131.2, C132.2, C133.2, C134.2, C135.2, CANT1.2, CANT2.2, CIN1.2, CIN2.2, COUT1.2, COUT2.2, C_ADC1.2, C_DVDD1.2, C_DVDD2.2, C_DVDD3.2, C_IOBULK1.2, C_IOVDD1.2, C_IOVDD2.2, C_IOVDD3.2, C_IOVDD4.2, C_IOVDD5.2, C_IOVDD6.2, C_IOVDD7.2, C_IOVDD8.2, C_QSPI1.2, C_USB1.2, C_USB2.2, C_USBOTP1.2, IC1.6 (GND), IC2.8 (VSS_1), IC2.9 (VSS_2), J1.1, J4.A1 (GND), J4.A12 (GND), J4.B1 (GND), J4.B12 (GND), J4.S1 (SHIELD), J5.2, J6.3, J6.5, J6.9, J7.2, J10.A1 (GND), J10.A12 (GND), J10.B1 (GND), J10.B12 (GND), J10.S1 (Shield), J11.3, J11.5, J11.9, J14.1, J15.1, J16.3, J16.5, J16.9, J18.1, J19.1, J19.5, J19.7, J20.A1 (GND), J20.A12 (GND), J20.B1 (GND), J20.B12 (GND), J21.8, J21.10, J21.11, J22.1, J23.8, NT1.2, R11.2, R20.1, R21.1, R22.1, R26.1, R27.1, R38.1, R47.2, R48.2, R52.2, R61.2, R62.2, R63.2, R64.2, R65.2, R68.2, R69.2, R70.2, RCC1.2, RCC2.2, RCC3.1, RCC4.1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
unnamed: J17.A5 (CC1), RCC3.2
unnamed: J17.B5 (CC2), RCC4.2
unnamed: J17.A6 (D+), J17.B6 (D+), R28.2
unnamed: J17.A7 (D-), J17.B7 (D-), R29.2
unnamed: J17.A1 (GND), J17.A12 (GND), J17.B1 (GND), J17.B12 (GND), J17.S1 (SHIELD)
unnamed: J18.2, U20.3 (VCAL/CH0)
unnamed: R13.1, U9.4 (I/O2)
unnamed: R14.1, U9.6 (I/O1)
unnamed: R29.1, U18.27 (USB_D_N)
unnamed: R28.1, U18.28 (USB_D_P)
unnamed: C_USB2.1, J17.A4 (VBUS), J17.A9 (VBUS), J17.B4 (VBUS), J17.B9 (VBUS), U18.25 (VDD_USB)
unnamed: TP4.1, U20.2 (CH1)

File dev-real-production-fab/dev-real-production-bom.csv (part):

"Refs","Value","Footprint","Qty","DNP"
"C1","4.7uF / >=10V","Capacitor_SMD:C_0805_2012Metric","1",""
"C2","2.2uF / >=10V","Capacitor_SMD:C_0603_1608Metric","1",""
"C3,C5,C65,C69,C70,C75,C98,C99,C102,C106,C107,C109,C110,C112-C116,C119-C126,C129,C130,C134","100nF","Capacitor_SMD:C_0603_1608Metric","29",""
"C4,C135","4.7nF","Capacitor_SMD:C_0603_1608Metric","2",""
"C6,C7","15pF C0G","RP2350B_minimal_hier:C_0402_1005Metric","2",""
"C8-C10","4.7uF 6.3V X5R","RP2350B_minimal_hier:C_0402_1005Metric","3",""
"C11,C12,C14,C16,C17,C20,C34,C35,C45","0.1uF","Capacitor_SMD:C_0402_1005Metric","9",""
"C13,C15,C18","22uF","Capacitor_SMD:C_0603_1608Metric","3",""
"C19,C26,C27,C37,C40,C49,C54,C61","1uF","Capacitor_SMD:C_0402_1005Metric","8",""
"C21-C23","100pF","Capacitor_SMD:C_0201_0603Metric","3",""
"C24,C25","4.7pF","Capacitor_SMD:C_0402_1005Metric","2",""
"C28,C39","0.22uF","Capacitor_SMD:C_0402_1005Metric","2",""
"C29,C30","22pF","Capacitor_SMD:C_0402_1005Metric","2",""
"C31,C33,C41-C43","2.2uF","Capacitor_SMD:C_0402_1005Metric","5",""
"C32","0.047uF","Capacitor_SMD:C_0402_1005Metric","1",""
"C36,C38,C44,C46,C47","10uF","Capacitor_SMD:C_0402_1005Metric","5",""
"C48","4.7uF","Capacitor_SMD:C_0402_1005Metric","1",""
"C50,C52,C53,C60,C71,C76,C77,C83","10uF","Capacitor_SMD:C_0603_1608Metric","8",""
"C51,C55-C59,C62,C63","100nF","Capacitor_SMD:C_0402_1005Metric","8",""
"C64,C67,C74","10uF","Capacitor_SMD:C_0805_2012Metric","3",""
"C66","22uF","Capacitor_SMD:C_0805_2012Metric","1",""
"C68,C78,C84,C89,C103,C118,C131,C132","1uF","Capacitor_SMD:C_0603_1608Metric","8",""
"C72,C79,C81,C85-C88,C92,C93","100n","Capacitor_SMD:C_0603_1608Metric","9",""
"C73","100nF BIAS","Capacitor_SMD:C_0603_1608Metric","1",""
"C80","100nF AVDD","Capacitor_SMD:C_0603_1608Metric","1",""
"C82","100nF DVDD","Capacitor_SMD:C_0603_1608Metric","1",""
"C90","100nF VDD","Capacitor_SMD:C_0603_1608Metric","1",""
"C91","100nF VOCM","Capacitor_SMD:C_0603_1608Metric","1",""
"C94","1nF VDD HF","Capacitor_SMD:C_0402_1005Metric","1",""
"C95","22pF C0G","Capacitor_SMD:C_0402_1005Metric","1",""
"C96,C101","12pF","Capacitor_SMD:C_0603_1608Metric","2",""
"C97,C105,C111","2.2uF low-ESR","Capacitor_SMD:C_0603_1608Metric","3",""
"C100,C104","4.7uF","Capacitor_SMD:C_0603_1608Metric","2",""
"C108,C117","6.8pF","Capacitor_SMD:C_0603_1608Metric","2",""
"C127,C128","18pF","Capacitor_SMD:C_0603_1608Metric","2",""
"C133","2.2uF","Capacitor_SMD:C_0603_1608Metric","1",""
"CIN1","10uF / >=10V","Capacitor_SMD:C_1210_3225Metric","1",""
"CIN2","39uF / >=10V","Capacitor_SMD:C_1210_3225Metric","1",""
"COUT1","47uF / >=6.3V","Capacitor_SMD:C_1210_3225Metric","1",""
"COUT2","100uF / >=6.3V","Capacitor_SMD:C_TODO_SELECT_100uF","1",""
"CSS1","12nF","Capacitor_SMD:C_0603_1608Metric","1",""
"CSVIN1","1uF / >=10V","Capacitor_SMD:C_0805_2012Metric","1",""
"C_ADC1,C_DVDD1-C_DVDD3,C_IOVDD1-C_IOVDD8,C_QSPI1,C_USB1,C_USB2,C_USBOTP1","100nF","RP2350B_minimal_hier:C_0402_1005Metric","16",""
"C_IOBULK1","10uF","RP2350B_minimal_hier:C_0402_1005Metric","1",""
"FB1,FB2,FB4-FB6","600R@100MHz","Inductor_SMD:L_0603_1608Metric","5",""
"FB3","600R@100MHz","Inductor_SMD:L_0805_2012Metric","1",""
"FB7-FB9","600R@100MHz","Inductor_SMD:L_0603_1608Metric_Pad0.95x0.95mm_HandSolder","3",""
"IC1","ICM-42670-P","ICM-42670-P:ICM42670P","1",""
"IC2","ENS161-BLGT_LGA9_T&R_1k5","ENS161-BLGT_LGA9_T&R_1k5:ENS161BLGTLGA9TR1k5","1",""
"J1","VIN_IN","TerminalBlock_Phoenix:TerminalBlock_Phoenix_MKDS-1,5-2_1x02_P5.00mm_Horizontal","1",""
"J2","TP_EN_PG","TerminalBlock_Phoenix:TerminalBlock_Phoenix_MKDS-1,5-2_1x02_P5.00mm_Horizontal","1",""
"J3","TP_SW_FB","TerminalBlock_Phoenix:TerminalBlock_Phoenix_MKDS-1,5-2_1x02_P5.00mm_Horizontal","1",""
"J4,J17","USB-C Receptacle USB2","Connector_USB:USB_C_Receptacle_GCT_USB4105-xx-A_16P_TopMnt_Horizontal","2",""
"J5","Conn_01x03_Pin","Connector_PinSocket_2.54mm:PinSocket_1x03_P2.54mm_Vertical","1",""
"J6","ARM_Cortex_Debug_10","Connector_PinHeader_1.27mm:PinHeader_2x05_P1.27mm_Vertical","1",""
"J7","SMA_ANT_50OHM","Connector_Coaxial:SMA_Molex_73251-2120_EdgeMount_Horizontal","1",""
"J8","3V3_IN","Connector_PinHeader_2.54mm:PinHeader_1x02_P2.54mm_Vertical","1",""
"J10","USB-C USB2 DEBUG","Connector_USB:USB_C_Receptacle_GCT_USB4105-xx-A_16P_TopMnt_Horizontal","1",""
"J11,J16","ARM_JTAG_10","Connector_PinHeader_1.27mm:PinHeader_2x05_P1.27mm_Vertical","2",""
"J12","SOP0_SELECT","Connector_PinHeader_2.54mm:PinHeader_1x03_P2.54mm_Vertical","1",""
"J13","SOP1_SELECT","Connector_PinHeader_2.54mm:PinHeader_1x03_P2.54mm_Vertical","1",""
"J14,J15","Conn_01x03","Connector_PinHeader_2.54mm:PinHeader_1x03_P2.54mm_Vertical","2",""
"J18","Conn_01x03_Pin","Connector_PinHeader_2.54mm:PinHeader_1x03_P2.54mm_Vertical","1",""
"J19","Cortex SWD/JTAG","Connector_PinHeader_1.27mm:PinHeader_2x05_P1.27mm_Vertical","1",""
"J20","USB-C USB2 DEVICE","Connector_USB:USB_C_Receptacle_GCT_USB4105-xx-A_16P_TopMnt_Horizontal","1",""
"J21","HR911105A MAGJACK","Connector_RJ:RJ45_Hanrun_HR911105A","1",""
"J22","Conn_02x10_Counter_Clockwise","Connector_PinHeader_2.54mm:PinHeader_2x10_P2.54mm_Vertical","1",""
"J23","Conn_02x04_Odd_Even","Connector_PinHeader_2.54mm:PinHeader_2x04_P2.54mm_Vertical","1",""
"L1","1uH LMLP07C7M1R0DTAS, Idc 15A / Isat 20A","Inductor_SMD:L_Kyocera_LMLP07C7D_7.3x6.6mm","1",""
"L2","3.3uH Abracon AOTA-B201610S3R3-101-T","RP2350B_minimal_hier:L_Abracon_AOTA-B201610S_2.0x1.6mm","1",""
"NT1","AGND_to_PGND_single_point","NetTie:NetTie-2_SMD_Pad0.5mm","1",""
"R1,R35,R43,R46-R49,R62,REN1","100k","Resistor_SMD:R_0603_1608Metric","9",""
"R2","60.4k","Resistor_SMD:R_0603_1608Metric","1",""
"R3,R4","2R","Resistor_SMD:R_0603_1608Metric","2",""
"R5","24.3k","Resistor_SMD:R_0603_1608Metric","1",""
"R6,R70,R71","1k","RP2350B_minimal_hier:R_0402_1005Metric","3",""
"R7,R8,R28,R29","27R","RP2350B_minimal_hier:R_0402_1005Metric","4",""
"R9","33R 1%","RP2350B_minimal_hier:R_0402_1005Metric","1",""
"R10","100k","Resistor_SMD:R_0402_1005Metric","1",""
"R11,R12","10k","Resistor_SMD:R_0402_1005Metric","2",""
"R13,R14","27","Resistor_SMD:R_0402_1005Metric","2",""
"R15,R16","0","Resistor_SMD:R_0402_1005Metric","2",""
"R17","47.5k","Resistor_SMD:R_0402_1005Metric","1",""
"R18,R19","2M","Resistor_SMD:R_0402_1005Metric","2",""
"R20-R22","75R","Resistor_SMD:R_0402_1005Metric","3",""
"R23-R25,R27","2.2k","Resistor_SMD:R_0603_1608Metric","4",""
"R26","3.8k","Resistor_SMD:R_0402_1005Metric","1",""
"R30-R34","47k","Resistor_SMD:R_0603_1608Metric","5",""
"R36,R37,R39,R40","1k 0.1%","Resistor_SMD:R_0402_1005Metric","4",""
"R38","10k 1%","Resistor_SMD:R_0603_1608Metric","1",""
"R41,R42","33R","Resistor_SMD:R_0402_1005Metric","2",""
"R44,R50","0R","Resistor_SMD:R_0603_1608Metric","2",""
"R45,R65","1M","Resistor_SMD:R_0603_1608Metric","2",""
"R51-R55,R57,RPG1","10k","Resistor_SMD:R_0603_1608Metric","7",""
"R56","1.5k","Resistor_SMD:R_0603_1608Metric","1",""
"R58,R59","22R","Resistor_SMD:R_0603_1608Metric","2",""
"R60","100R","Resistor_SMD:R_0603_1608Metric","1",""
"R61","12.1k 1%","Resistor_SMD:R_0603_1608Metric","1",""
"R63,R64","5.1k","Resistor_SMD:R_0603_1608Metric","2",""
"R66,R67","330R","Resistor_SMD:R_0603_1608Metric","2",""
"R68,R69","10k STRAP LOW","Resistor_SMD:R_0603_1608Metric","2",""
"RANT1","0R","Resistor_SMD:R_0402_1005Metric","1",""
"RBOT1","665R","Resistor_SMD:R_0603_1608Metric","1",""
"RCC1-RCC4","5.1k","RP2350B_minimal_hier:R_0402_1005Metric","4",""
"RCL1","2.21k","Resistor_SMD:R_0603_1608Metric","1",""
"RTOP1","3.00k","Resistor_SMD:R_0603_1608Metric","1",""
"TP1","AR_TP","TestPoint:TestPoint_Pad_D1.0mm","1",""
"TP2","AG_TP","TestPoint:TestPoint_Pad_D1.0mm","1",""
"TP3","AB_TP","TestPoint:TestPoint_Pad_D1.0mm","1",""
"TP4,TP5","VCM","TestPoint:TestPoint_Pad_D1.0mm","2",""
"TP6","VREF","TestPoint:TestPoint_Pad_D1.0mm","1",""
"TP7","AVDD_1V8","TestPoint:TestPoint_Pad_D1.0mm","1",""
"TP8","ADC_VIN_P","TestPoint:TestPoint_Pad_D1.0mm","1",""
"TP9","ADC_VIN_N","TestPoint:TestPoint_Pad_D1.0mm","1",""
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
